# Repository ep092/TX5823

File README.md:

# TX5823
FPV Sender mit Kanalwahl und konfiguration über SPI. Integriertes OSD mit MAX7456 und Spannungswandlern für 5V, 3,3V und Vorbereitung für 12V, über einen Eingangsspannungsbereich von 8V bis 25.2V.
Das OSD ist kompatibel zu minimosd und wird mit dessen Firmware betrieben und mit der entsprechenden Software konfiguriert.
Die Kanalwahl folgt über einen freien Empfängerkanal.
Zusätzlich ist ein Infrarotauslöser für Canonkameras vorgesehen.

-------------------
Status:
- schaltplan fertig
- layout fertig
- platine bestellt
- Bauteile bestellt
- platine bestückt
- Tests erfolgreich

-------------------
Steckerbelegung 3-reihige Pinleiste(Orientierung Pinleiste nach links, oben 1):

untere Reihe, mittlere Reihe, obere Reihe

1. GND, NC, Video in
2. GND, NC, Sound in
3. GND, NC, PWM in
4. Infrator LED -, NC, Infrarot LED +
5. GND, 5V out, NC
6. GND. 5V out, NC
7. GND, 12V out (optional), NC
8. GND, 12V out (optional), NC

-------------------

Steckerbelegung mavlink Stecker

1. DTR (für Reset über USB)
2. TX (Atmega Daten Senden)
3. RX (Atmega Daten Empfangen)
4. 5/3,3V
5. GND

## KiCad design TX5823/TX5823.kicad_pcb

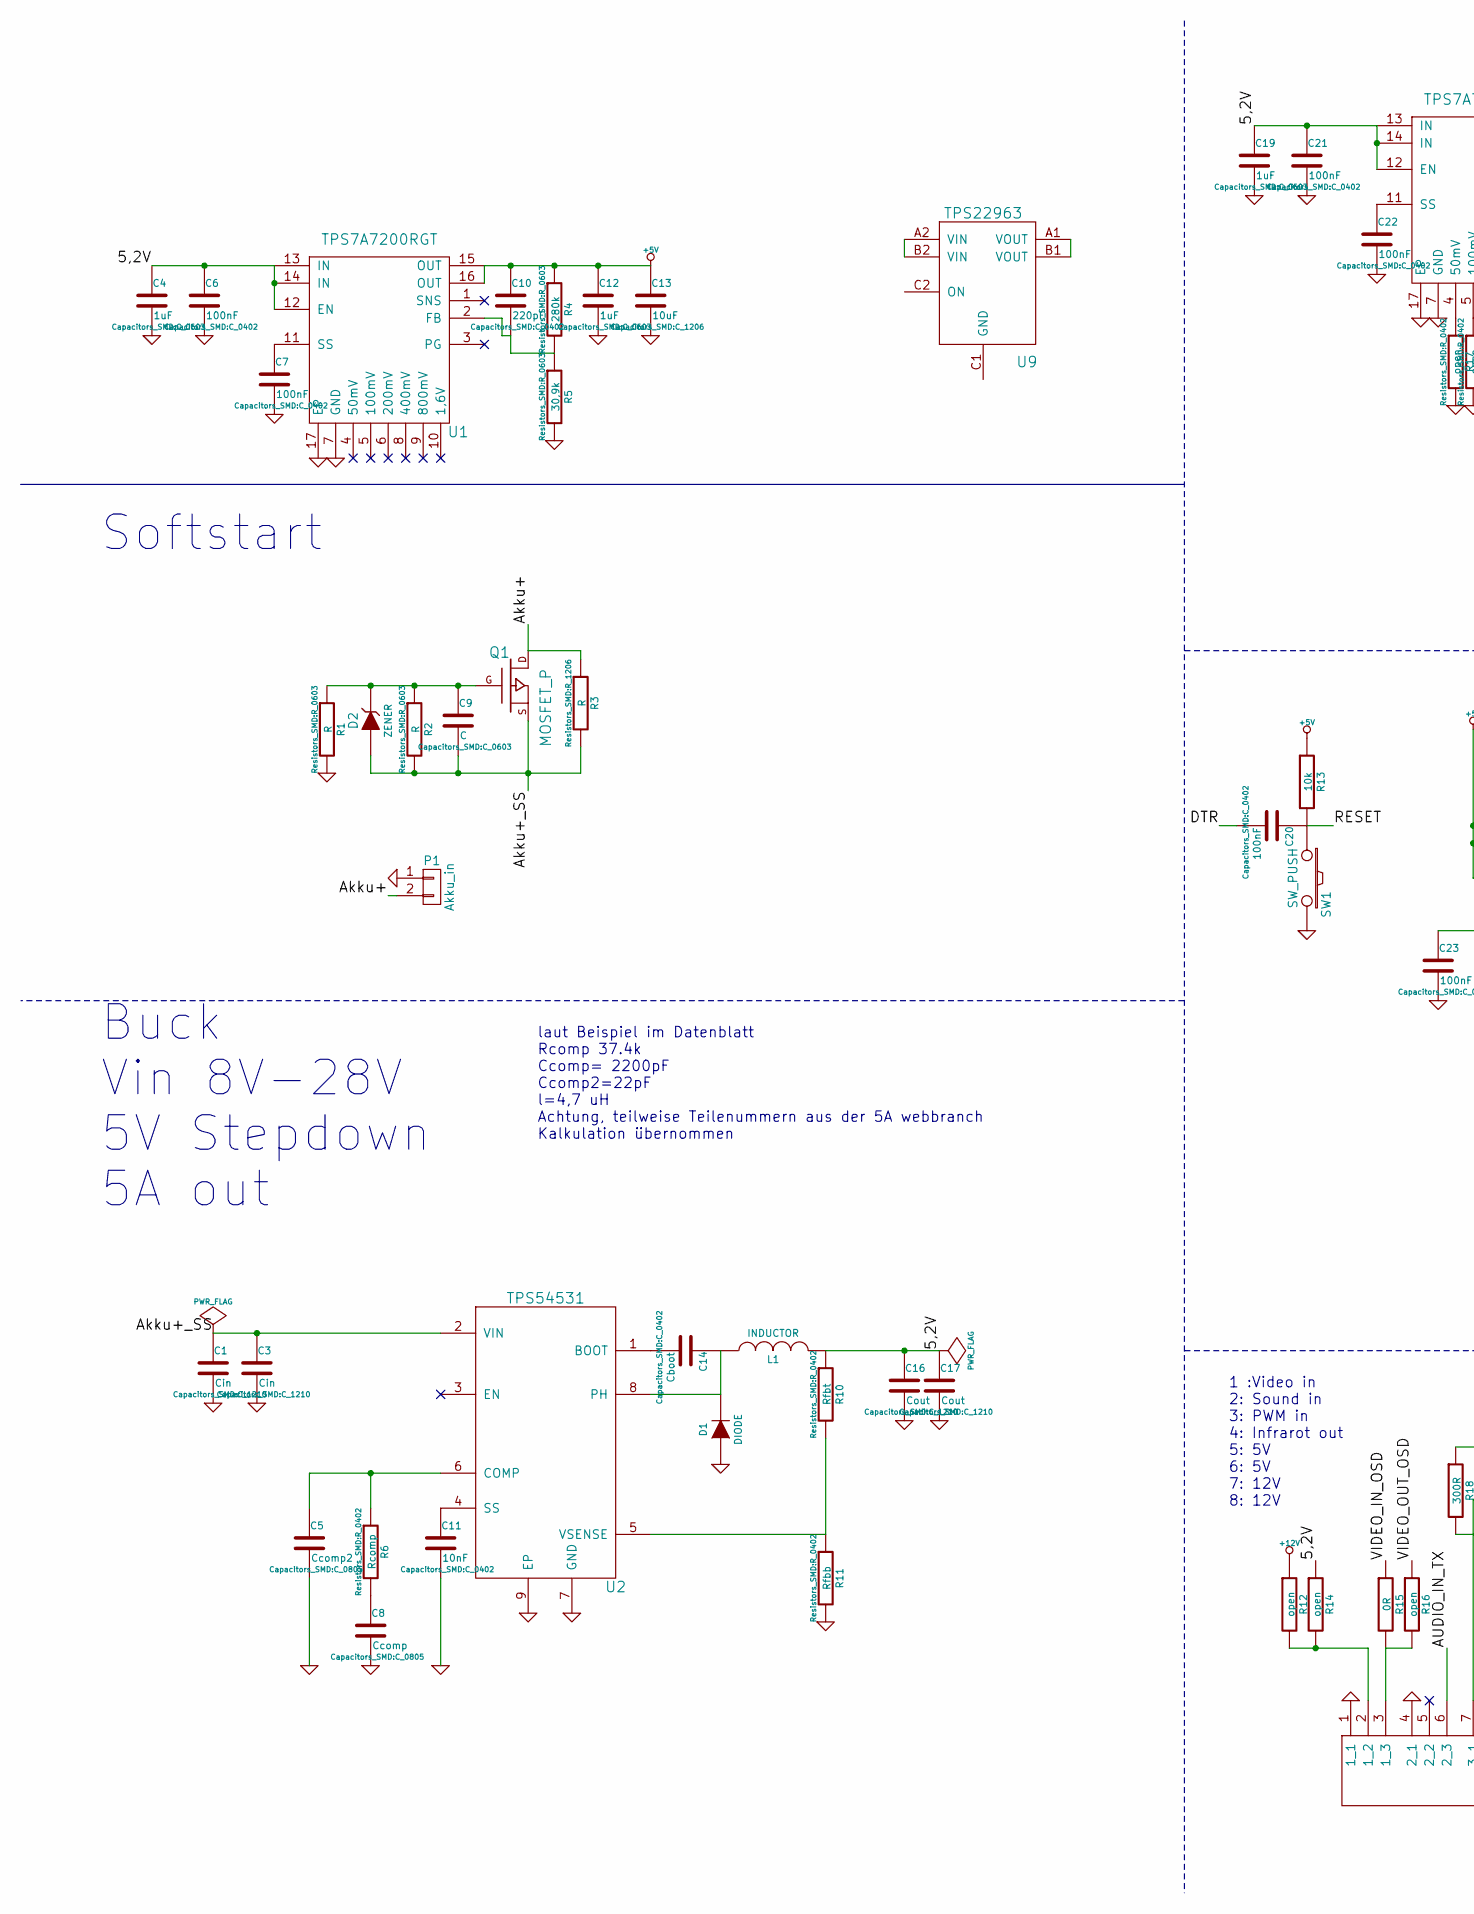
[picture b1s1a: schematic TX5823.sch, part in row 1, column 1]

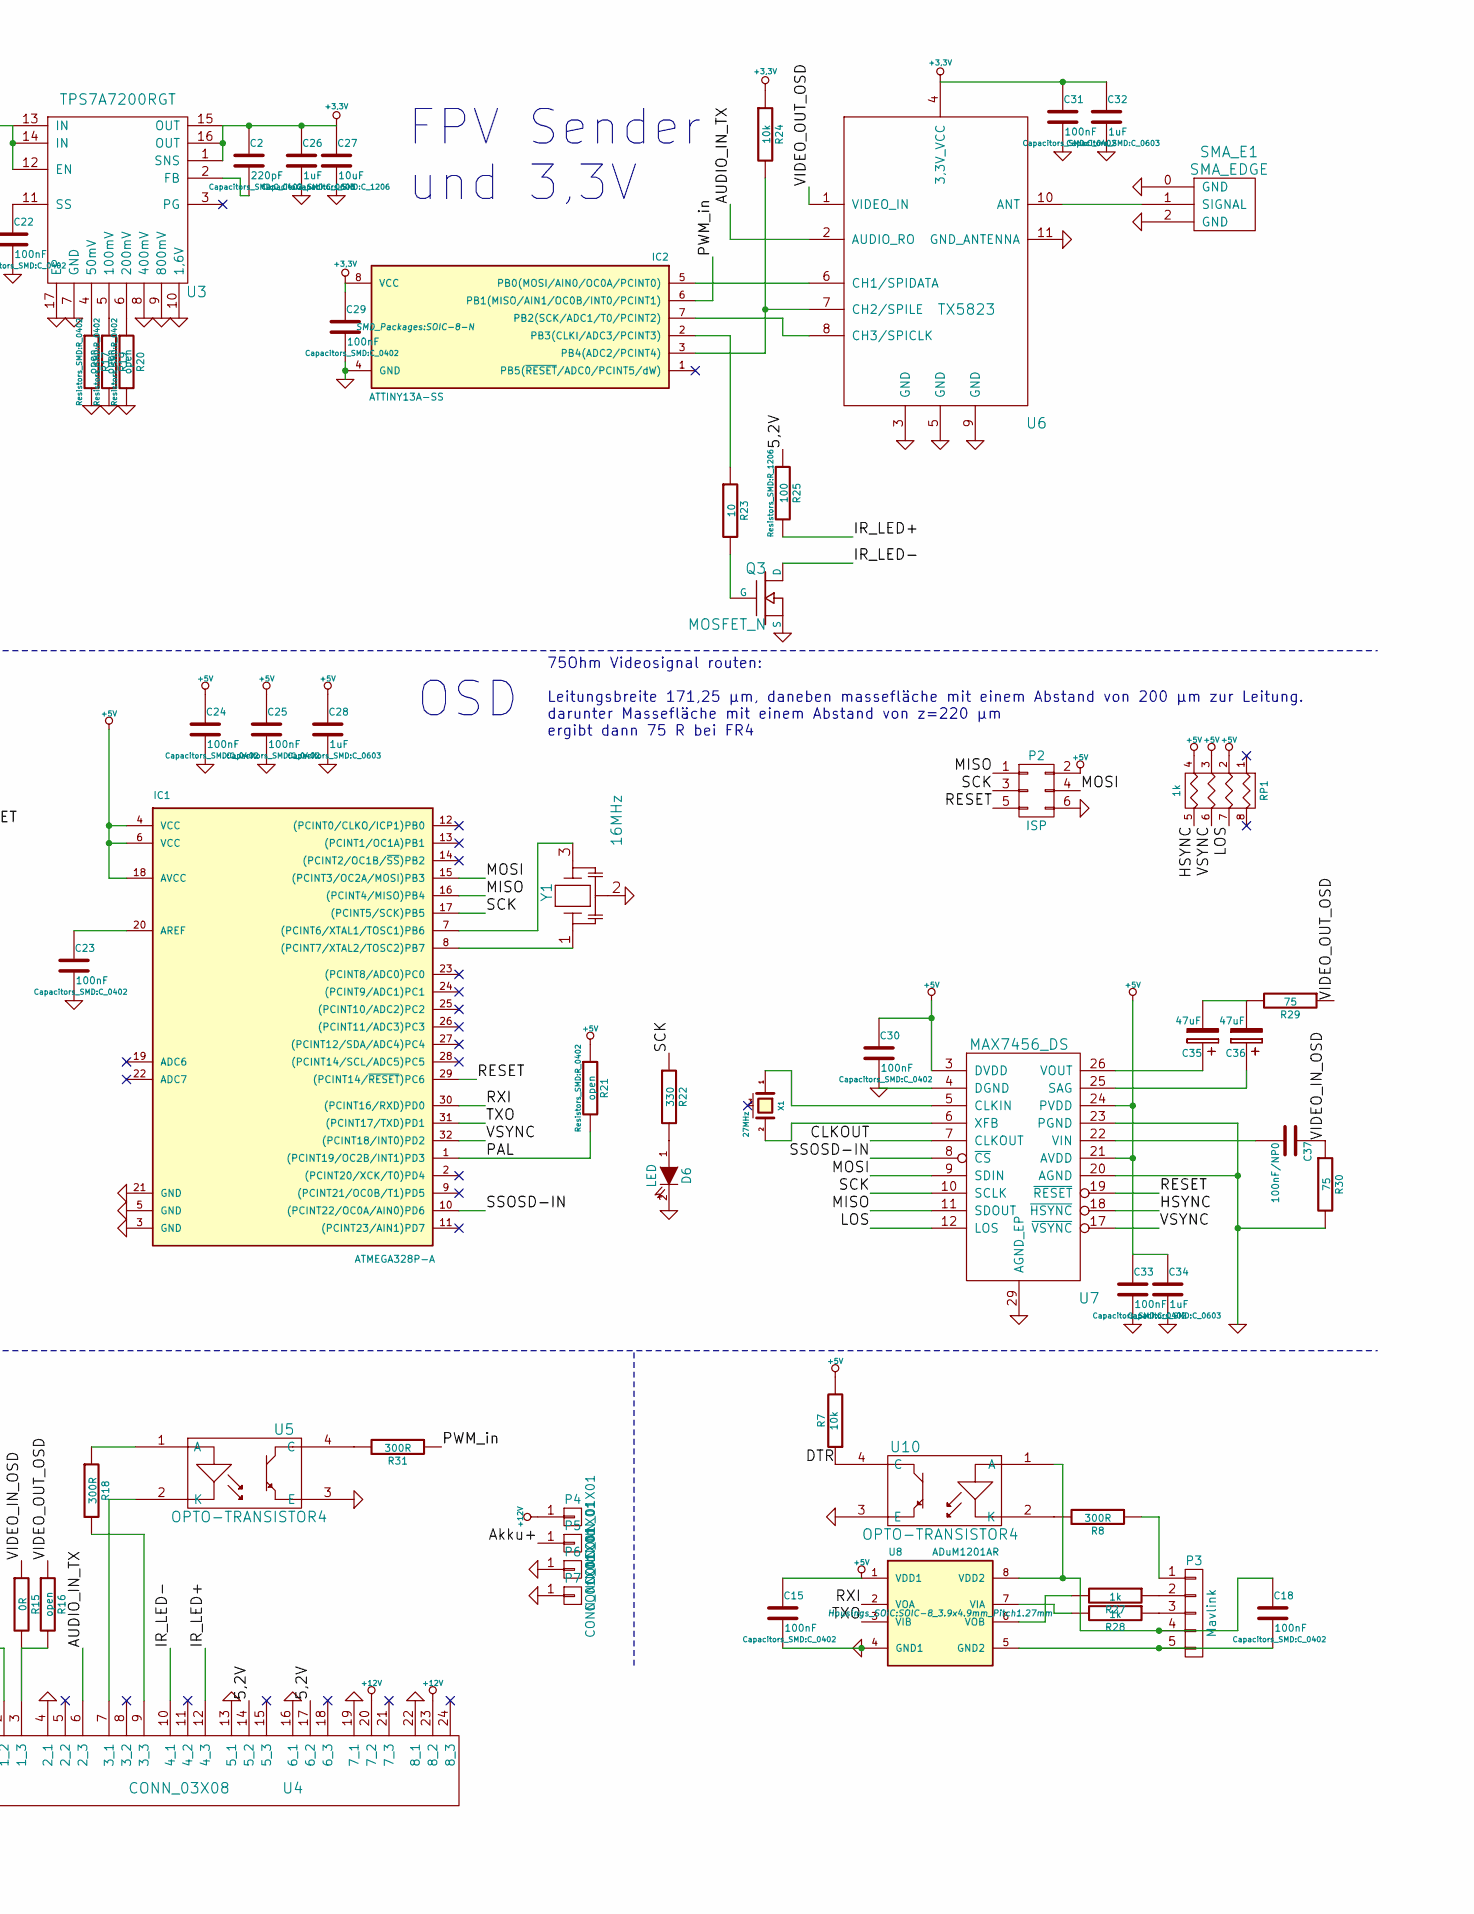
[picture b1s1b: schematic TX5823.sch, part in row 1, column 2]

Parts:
C1, C3: Cin; C_1210
C2, C10: 220pF; C_0402
C4, C12, C19, C26, C28, C32, C34: 1uF; C_0603
C5: Ccomp2; C_0805
C6, C7, C15, C18, C20, C21, C22, C23, C24, C25, C29, C30, C31, C33: 100nF; C_0402
C8: Ccomp; C_0805
C9: C; C_0603
C11: 10nF; C_0402
C13, C27: 10uF; C_1206
C14: Cboot; C_0402
C16, C17: Cout; C_1210
C35, C36: 47uF; TantalC_SizeB_EIA-3528_Reflow
C37: 100nF/NP0; C_1206
D1: DIODE; POWERDI5
D2: ZENER; Diode-MiniMELF_Standard
D6: LED; LED-0603
IC1: ATMEGA328P-A; TQFP-32_7x7mm_Pitch0.8mm
IC2: ATTINY13A-SS; SOIC-8-N
L1: INDUCTOR; Choke_SMD_Wuerth-WE-PD-Typ-LS_Handsoldering
P1: Akku_in; Socket_Strip_Angled_1x02
P2: ISP; micro_match3x2
P3: Mavlink; Connector_Molex_PicoBlade_53261-0571
P4, P5, P6, P7: CONN_01X01; Pin_Header_Straight_1x01
Q1: MOSFET_P; SO8_WITH_EP
Q3: MOSFET_N; SOT23_GDS
R1, R2: R; R_0603
R3: R; R_1206
R4: 280k; R_0603
R5: 30,9k; R_0603
R6: Rcomp; R_0402
R7, R13, R24: 10k; R_0603
R8: 300R; R_0603
R10: Rfbt; R_0402
R11: Rfbb; R_0402
R12, R14, R16: open; R_0603
R15: 0R; R_0603
R17, R19, R20, R21: open; R_0402
R18: 300R; R_0805
R22: 330; R_0805
R23: 10; R_0805
R25: 100; R_1206
R27, R28: 1k; R_0603
R29, R30: 75; C_0805
R31: 300R; C_0805
RP1: 1k; R_Array_Concave_4x0603
SMA_E1: SMA_EDGE
SW1: SW_PUSH; EVQP7A
U1, U3: TPS7A7200RGT; QFN-16-1EP_3x3mm_Pitch0.5mm
U2: TPS54531; SO8_EP
U4: CONN_03X08; Conn_03x08
U5, U10: OPTO-TRANSISTOR4; SO-4
U6: TX5823
U7: MAX7456_DS; TSSOP-28_4.4x9.7mm_Pitch0.65mm_EP
U8: ADuM1201AR; SOIC-8_3.9x4.9mm_Pitch1.27mm
U9: TPS22963; DSBGS(6)
X1: 27MHz; CRYSTAL_MT
Y1: 16MHz; CerOsc_3,2x1,3

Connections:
+3.3V: C2.1, C26.1, C27.1, C29.1, C31.1, C32.1, IC2.8 (VCC), R24.1, U3.1 (SNS), U3.15 (OUT), U3.16 (OUT), U6.4 (3,3V_VCC)
+5V: C10.1, C12.1, C13.1, C15.1, C24.1, C25.1, C28.1, C30.1, C33.1, C34.1, IC1.4 (VCC), IC1.6 (VCC), IC1.18 (AVCC), P2.2, R4.1, R7.2, R13.1, R21.1, RP1.2, RP1.3, RP1.4, U1.15 (OUT), U1.16 (OUT), U7.3 (DVDD), U7.21 (AVDD), U7.24 (PVDD), U8.1 (VDD1)
+12V: P4.1, R12.1, U4.20 (7_2), U4.23 (8_2)
/5,2V: C4.1, C6.1, C16.1, C17.1, C19.1, C21.1, L1.2, R10.1, R14.1, R25.1, U1.12 (EN), U1.13 (IN), U1.14 (IN), U3.12 (EN), U3.13 (IN), U3.14 (IN), U4.14 (5_2), U4.17 (6_2)
/AUDIO_IN_TX: U4.6 (2_3), U6.2 (AUDIO_RO)
/Akku+: P1.2, P5.1, Q1.D, R3.1
/Akku+_SS: C1.1, C3.1, C9.2, D2.1 (A), Q1.S, R2.2, R3.2, U2.2 (VIN)
/CLKOUT: U7.7 (CLKOUT)
/DTR: C20.2, R7.1, U10.4 (C)
/HSYNC: RP1.5 (R4), U7.18 (~HSYNC)
/IR_LED+: R25.2, U4.12 (4_3)
/IR_LED-: Q3.D, U4.10 (4_1)
/LOS: RP1.7 (R2), U7.12 (LOS)
/MISO: IC1.16 ((PCINT4/MISO)PB4), P2.1, U7.11 (SDOUT)
/MOSI: IC1.15 ((PCINT3/OC2A/MOSI)PB3), P2.4, U7.9 (SDIN)
/PAL: IC1.1 ((PCINT19/OC2B/INT1)PD3), R21.2
/PWM_in: IC2.6 (PB1(MISO/AIN1/OC0B/INT0/PCINT1)), R31.1
/RESET: C20.1, IC1.29 ((PCINT14/~RESET~)PC6), P2.5, R13.2, SW1.1, U7.19 (~RESET)
/RXI: IC1.30 ((PCINT16/RXD)PD0), U8.2 (VOA)
/SCK: IC1.17 ((PCINT5/SCK)PB5), P2.3, R22.1, U7.10 (SCLK)
/SSOSD-IN: IC1.10 ((PCINT22/OC0A/AIN0)PD6), U7.8 (~CS)
/TXO: IC1.31 ((PCINT17/TXD)PD1), U8.3 (VIB)
/VIDEO_IN_OSD: C37.1, R15.1, R30.1
/VIDEO_OUT_OSD: R16.1, R29.1, U6.1 (VIDEO_IN)
/VSYNC: IC1.32 ((PCINT18/INT0)PD2), RP1.6 (R3), U7.17 (~VSYNC)
GND: C1.2, C3.2, C4.2, C5.2, C6.2, C7.2, C8.2, C11.2, C12.2, C13.2, C15.2, C16.2, C17.2, C19.2, C21.2, C22.2, C23.2, C24.2, C25.2, C26.2, C27.2, C28.2, C29.2, C30.2, C31.2, C32.2, C33.2, C34.2, D1.1 (A), D6.2 (K), IC1.3 (GND), IC1.5 (GND), IC1.21 (GND), IC2.4 (GND), P1.1, P2.6, P6.1, P7.1, Q3.S, R1.2, R5.2, R11.2, R17.2, R19.2, R20.2, R30.2, SMA_E1.0 (GND), SMA_E1.2 (GND), SW1.2, U1.7 (GND), U1.17 (EP), U2.7 (GND), U2.9 (EP), U3.7 (GND), U3.8 (400mV), U3.9 (800mV), U3.10 (1,6V), U3.17 (EP), U4.1 (1_1), U4.4 (2_1), U4.13 (5_1), U4.16 (6_1), U4.19 (7_1), U4.22 (8_1), U5.3 (E), U6.3 (GND), U6.5 (GND), U6.9 (GND), U6.11 (GND_ANTENNA), U7.4 (DGND), U7.20 (AGND), U7.23 (PGND), U7.29 (AGND_EP), U8.4 (GND1), U10.3 (E), Y1.2
unnamed: C2.2, U3.2 (FB)
unnamed: C5.1, R6.1, U2.6 (COMP)
unnamed: C7.1, U1.11 (SS)
unnamed: C8.1, R6.2
unnamed: C9.1, D2.2 (K), Q1.G, R1.1, R2.1
unnamed: C10.2, R4.2, R5.1, U1.2 (FB)
unnamed: C11.1, U2.4 (SS)
unnamed: C14.1, D1.2 (K), L1.1, U2.8 (PH)
unnamed: C14.2, U2.1 (BOOT)
unnamed: C18.1, P3.4, U8.8 (VDD2), U10.1 (A)
unnamed: C18.2, P3.5, U8.5 (GND2)
unnamed: C22.1, U3.11 (SS)
unnamed: C23.1, IC1.20 (AREF)
unnamed: C35.1, U7.26 (VOUT)
unnamed: C35.2, C36.2, R29.2
unnamed: C36.1, U7.25 (SAG)
unnamed: C37.2, U7.22 (VIN)
unnamed: D6.1 (A), R22.2
unnamed: IC1.7 ((PCINT6/XTAL1/TOSC1)PB6), Y1.3
unnamed: IC1.8 ((PCINT7/XTAL2/TOSC2)PB7), Y1.1
unnamed: IC2.2 (PB3(CLKI/ADC3/PCINT3)), R23.1
unnamed: IC2.3 (PB4(ADC2/PCINT4)), R24.2, U6.7 (CH2/SPILE)
unnamed: IC2.5 (PB0(MOSI/AIN0/OC0A/PCINT0)), U6.6 (CH1/SPIDATA)
unnamed: IC2.7 (PB2(SCK/ADC1/T0/PCINT2)), U6.8 (CH3/SPICLK)
unnamed: P3.1, R8.1
unnamed: P3.2, R27.1
unnamed: P3.3, R28.1
unnamed: Q3.G, R23.2
unnamed: R8.2, U10.2 (K)
unnamed: R10.2, R11.1, U2.5 (VSENSE)
unnamed: R12.2, R14.2, U4.2 (1_2)
unnamed: R15.2, R16.2, U4.3 (1_3)
unnamed: R17.1, U3.4 (50mV)
unnamed: R18.1, U5.1 (A)
unnamed: R18.2, U4.9 (3_3)
unnamed: R19.1, U3.5 (100mV)
unnamed: R20.1, U3.6 (200mV)
unnamed: R27.2, U8.6 (VOB)
unnamed: R28.2, U8.7 (VIA)
unnamed: R31.2, U5.4 (C)
unnamed: SMA_E1.1 (SIGNAL), U6.10 (ANT)
unnamed: U4.7 (3_1), U5.2 (K)
unnamed: U7.5 (CLKIN), X1.1
unnamed: U7.6 (XFB), X1.2
unnamed: U9.A1 (VOUT), U9.B1 (VOUT)
unnamed: U9.A2 (VIN), U9.B2 (VIN)

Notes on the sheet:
Buck Vin 8V-28V 5V Stepdown 5A out
FPV Sender und 3,3V
OSD
laut Beispiel im Datenblatt Rcomp 37.4k Ccomp= 2200pF Ccomp2=22pF l=4,7 uH Achtung, teilweise Teilenummern aus der 5A webbranch Kalkulation übernommen
1 :Video in 2: Sound in 3: PWM in 4: Infrarot out 5: 5V 6: 5V 7: 12V 8: 12V
75Ohm Videosignal routen: Leitungsbreite 171,25 µm, daneben massefläche mit einem Abstand von 200 µm zur Leitung. darunter Massefläche mit einem Abstand von z=220 µm ergibt dann 75 R bei FR4
Softstart

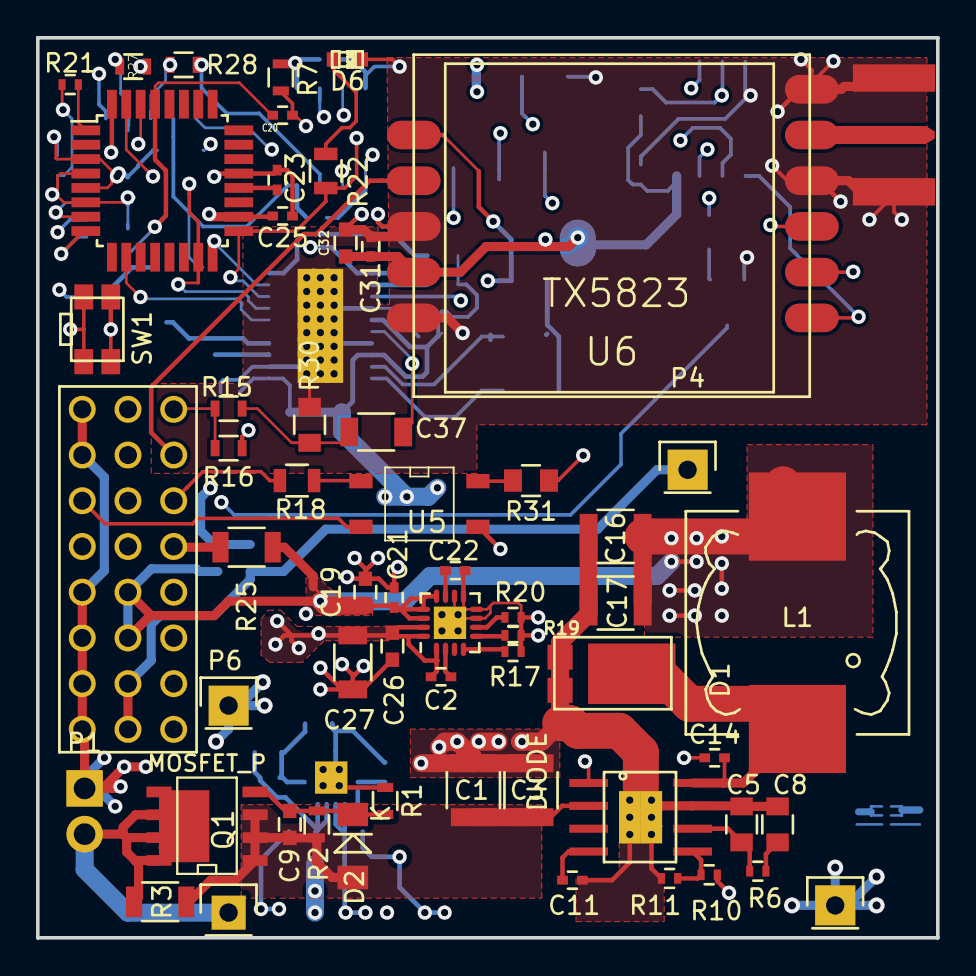
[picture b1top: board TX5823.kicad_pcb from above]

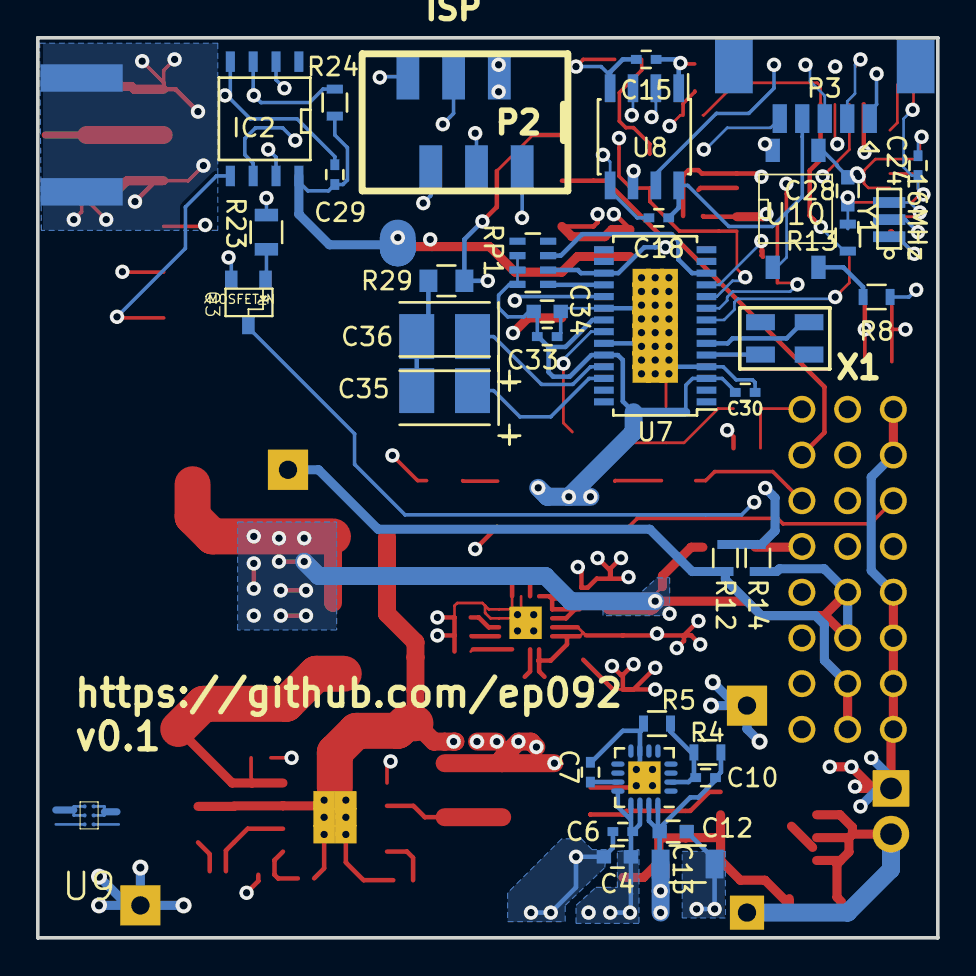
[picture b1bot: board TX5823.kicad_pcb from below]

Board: 4 copper layers, 50.0 x 50.0 mm, 96 parts (37 on the bottom side), 71 nets.

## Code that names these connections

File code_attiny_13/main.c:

//hfuse FB
//lfuse 7A

#include <avr/interrupt.h>
#include <avr/io.h>
#include <util/delay.h>
#include <avr/pgmspace.h>


//user defined:
#define IR_LED_PORT PORTB
#define IR_LED_DDR DDRB
#define IR_LED_PIN PB3

#define PWM_IN_PORT PORTB
#define PWM_IN_DDR DDRB
#define PWM_IN_PIN PB1

#define SPI_DATA_PORT PORTB
#define SPI_DATA_DDR DDRB
#define SPI_DATA_PIN PB0

#define SPI_LE_PORT PORTB
#define SPI_LE_DDR DDRB
#define SPI_LE_PIN PB4

#define SPI_CLOCK_PORT PORTB
#define SPI_CLOCK_DDR DDRB
#define SPI_CLOCK_PIN PB2

#define TIME_BETWEEN_PHOTOS 3000

//settings for pwm signal
#define PWM_VALUE_0_MIN	105	//min length for the signal (pulse) to be detectet as "middle"
#define PWM_VALUE_0_MAX 135	//max length for the signal (pulse) to be detectet as "middle"
#define PWM_VALUE_MIN 75	//min length of the signal (pulse)
#define PWM_VALUE_MAX 175	//max length of the signal (pulse)


//non user defined:
#define IR_LED_ON 		IR_LED_PORT |= (1 << IR_LED_PIN)
#define IR_LED_OFF 		IR_LED_PORT &= ~(1 << IR_LED_PIN)
#define SPI_DATA_LOW 		SPI_DATA_PORT &= ~(1 << SPI_DATA_PIN)
#define SPI_DATA_HIGH 		SPI_DATA_PORT |= (1 << SPI_DATA_PIN)
#define SPI_LE_LOW 		SPI_LE_PORT &= ~(1 << SPI_LE_PIN)
#define SPI_LE_HIGH 		SPI_LE_PORT |= (1 << SPI_LE_PIN)
#define SPI_CLOCK_LOW 		SPI_CLOCK_PORT &= ~(1 << SPI_CLOCK_PIN)
#define SPI_CLOCK_HIGH 		SPI_CLOCK_PORT |= (1 <<SPI_CLOCK_PIN)

// Channels to sent to the SPI registers
const uint16_t channelTable[] PROGMEM = {
	// CH 1 CH 2 	CH 3 	CH 4 	CH 5 	CH 6 	CH 7 	CH 8
	0x7981, 0x758D, 0x7199, 0x6DA5, 0x69B1, 0x65BD, 0x6209, 0x5E15, // Band A
	0x5F9D, 0x6338, 0x6713, 0x6AAE, 0x6E89, 0x7224, 0x75BF, 0x799A, // Band B
	0x5A21, 0x562D, 0x5239, 0x4E85, 0x7D35, 0x8129, 0x851D, 0x8911, // Band E
	0x610C, 0x6500, 0x68B4, 0x6CA8, 0x709C, 0x7490, 0x7884, 0x7C38, // Band F / Airwave
	0x510A, 0x5827, 0x5F84, 0x66A1, 0x6DBE, 0x751B, 0x7C38, 0x8395  // Band R / Raceband
};

volatile uint8_t pwm_value = 0 ;
volatile uint8_t new_data = 0 ;

void canon_shutter_now(void){
	for(int i=0; i<16; i++) { 
		IR_LED_ON;
		_delay_us(15);
		IR_LED_OFF;
		_delay_us(15);
		
	} 
	_delay_us(7330); 
	for(int i=0; i<16; i++) { 
		IR_LED_ON;
		_delay_us(15);
		IR_LED_OFF;
		_delay_us(15);
		
	}
}

void canon_shutter_delayed(void){
	for(int i=0; i<16; i++) { 
		IR_LED_ON;
		_delay_us(11);
		IR_LED_OFF;
		_delay_us(11);
		
	} 
	_delay_us(5360); 
	for(int i=0; i<16; i++) { 
		IR_LED_ON;
		_delay_us(11);
		IR_LED_OFF;
		_delay_us(11);
		
	}
}


void serial_send_bit_1(void){
	SPI_CLOCK_LOW;
	_delay_us(1);
	SPI_DATA_HIGH;
	_delay_us(1);
	SPI_CLOCK_HIGH;
	_delay_us(1);
	SPI_CLOCK_LOW;
	_delay_us(1);
}

void serial_send_bit_0(void)
{
	SPI_CLOCK_LOW;
	_delay_us(1);
	SPI_DATA_LOW;
	_delay_us(1);
	SPI_CLOCK_HIGH;
	_delay_us(1);
	SPI_CLOCK_LOW;
	_delay_us(1);
}

void serial_enable_low(void){
	_delay_us(1);
	SPI_LE_LOW;
	_delay_us(1);
}

void serial_enable_high(void){
	_delay_us(1);
	SPI_LE_HIGH;
	_delay_us(1);
}

void set_channel(uint8_t channel){
	uint8_t i;
	uint16_t channelData;

	channelData = pgm_read_word_near(channelTable + channel);
	// 25 bits of data
	// Order: A0-3, !R/W, D0-D19
	// A0=1, A1=0, A2=0, A3=0, RW=1, D0-19=0 

	// 20 bytes of register data are sent, but the MSB 4 bits are zeros
	// register address = 0x1, write, data0-15=channelData data15-19=0x4

	serial_enable_high();
	_delay_us(1);
	serial_enable_low();
	
	// register 0x1
	serial_send_bit_1();
	serial_send_bit_0();
	serial_send_bit_0();
	serial_send_bit_0();

	// write to register
	serial_send_bit_1();

	// D0-D15
	for (i = 16; i > 0; i--){
	// check if bit is high or low
	if (channelData & 0x1){
		serial_send_bit_1();
	}
	else{
		serial_send_bit_0();
	}

	// Shift bits along to check the next one
	channelData >>= 1;
	}

	// Remaining D16-D19
	serial_send_bit_0();
	serial_send_bit_0();
	serial_send_bit_1();
	serial_send_bit_0();

	// Finished clocking data in
	serial_enable_high();
	_delay_us(1);
}

void int0_init(void){
	MCUCR |= (1<<ISC00);	//Any logical change on INT0 generates an interrupt request
	GIMSK |= (1<<INT0);	//External Interrupt Request 0 Enable
}

void timer_init(void){
	TCCR0B |= (1<<CS01) | (1<<CS00); //prescaler 64
}

void init (void){
	IR_LED_DDR |= (1<<IR_LED_PIN);
	PWM_IN_PORT |= (1<<PWM_IN_PIN);
	SPI_DATA_DDR |= (1<<SPI_DATA_PIN);
	SPI_LE_DDR |= (1<<SPI_LE_PIN);
	SPI_CLOCK_DDR |= (1<<SPI_CLOCK_PIN);
	serial_enable_high();
	SPI_CLOCK_LOW;	
}

int main(void) {
	uint8_t pwm_pulse_now;
	uint8_t pwm_pulse_last;
	uint8_t channel = 8;		//channel at startup
	init();
	timer_init();
	int0_init();
	set_channel(channel);
	sei();
	canon_shutter_now();
	_delay_ms(1000);
	pwm_value = 0;
	new_data = 0;
	_delay_ms(100);
	while (1){
		//wait for new data and detect timeout at pwm_in
		for(uint8_t i = 0; new_data==0 && i<200; i++){
			_delay_ms(1);
		}
		if (new_data) {
			pwm_pulse_last = pwm_pulse_now;
			pwm_pulse_now = pwm_value;
			if (pwm_pulse_now > PWM_VALUE_MIN && pwm_pulse_now < PWM_VALUE_0_MIN){		//switch channel
				if (pwm_pulse_last > PWM_VALUE_0_MIN && PWM_VALUE_0_MAX < 180){		//detect "falling edge"
					channel++;
					if (channel >=15){	//limit to A- and B-Band 
						channel = 0;
					}
					set_channel(channel);	
					_delay_ms(200); 
				}
			
			} else if(pwm_pulse_now > PWM_VALUE_0_MAX && pwm_pulse_now < PWM_VALUE_MAX){	//do photo
				while (pwm_value >PWM_VALUE_0_MAX && pwm_value < PWM_VALUE_MAX){	
					canon_shutter_now();
					_delay_ms(TIME_BETWEEN_PHOTOS);			//time between pictures
				}
			}
			
		}else{
			pwm_value = 0;
			pwm_pulse_last = 0;
			pwm_pulse_now = 0;
		}
		
		new_data = 0;
	}	
}

//saves the length of the pwm_pulse to pwm_value
ISR ( INT0_vect) {
	uint8_t counter = TCNT0; //buffer timervalue  
	TCNT0 = 0; //reset timer
	if (TIFR0 & (1<<TOV0)){	//timeroverflow
		TIFR0 = _BV(TOV0);
		if (PINB & (1<<PWM_IN_PIN)){
			pwm_value = 0;
			new_data = 1;
		}
	} else {

		pwm_value = counter;
		new_data = 1;
	}		
}

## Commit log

2015-03-25 Datenblatt hinzugefügt
2015-03-27 Bauteile angelegt
2015-03-27 an Schaltplan weitergearbeitet
2015-03-28 an Schaltplan weitergearbeitet. 5V Buck
2015-03-28 Teilenummern und connectoren hinzugefügt
2015-03-28 an Steckern im Schaltplan weitergearbeitet
2015-03-28 Schaltplan bereit für review
2015-03-28 ERC errors weitestgehend korrigiert
2015-03-29 an Schaltplan weitergearbeitet footprints hinzugefügt
2015-03-29 weitere Footprints zugeordnet grobe Anordnung der Bauteiele im Layout
2015-03-29 sma buchse hinzugefügt
2015-03-29 Bauteile grob angeordnet
2015-03-30 12V Wandler entfernt
2015-03-30 an Layout gearbeitet
2015-04-03 Layout fertig bis auf startup teil
2015-04-04 zusätzlicher LDO für OSD hinzugefügt Softstart hinzugefügt
2015-04-04 Verbindungspunkte für 12V BuckBoost Aufsteckplatine hinzugefügt
2015-04-04 Bestückungsdruck ausgerichtet
2015-04-04 DSBGA(&) Footprint für Löttests hinzugefügt. Keine relevanz für diese Platine
2015-04-04 Lötstop richtig eingestellt
2015-04-04 logo hinzugefügt
2015-04-04 Vias vom Rand weggerückt github link hinzugefügt
2015-04-04 letzte Änderungen für Fertigung Gerberdaten hinzugefügt
2015-04-05 mavlink isolierung überarbeitet. adum hinzugefüt
2015-04-05 footprint adum angepasst
2015-04-05 mavlink und adum geroutet
2015-04-05 5V Anbindung Atmel verbessert Bestückungsdruck hinzugefügt
2015-04-05 Neue Fertigungsdateien hinzugefügt
2015-05-18 fertigungsdaten, gerberfiles und attiny13a programm hinzugefügt
2015-05-18 fehlerhafte gerberdateien gelöscht Readme aktualisiert
2015-05-26 code für attiny auf testfähigen stand gebracht
2015-05-26 kanalwahl mit for schleife getestet
2015-05-26 fotoauslösung und kanalwechsel über pwm hinzugefügt - ungetestet
2015-05-27 programm vorerst fertiggestellt. funktioniert auf dem teststand.
2015-05-30 Timing für Kameraauslösung angepasst. Kameraauslösung und Kanalwahl getestet.
2015-08-06 readme überarbeitet attiny code angepasst
2015-08-06 readme aufzählung geändert
2015-08-06 aufzählung geändert
2015-08-11 Update README.md
    Fehler behoben, Steckerbelegung mavlink hinzugefügt
